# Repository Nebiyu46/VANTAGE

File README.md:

# VANTAGE

**V**ibration **AN**alysis **T**ool for **A**ppliance dia**G**nostic **E**valuation

A portable, battery-powered diagnostic instrument for predictive maintenance of domestic washing machines.

---

**Author:** Nebiyu Hailu  
**Course:** Design of Electronic Devices and Systems

## Overview

VANTAGE implements predictive maintenance by analyzing the acoustic and vibrational "fingerprint" of washing machines. Unlike reactive repair strategies, it enables proactive monitoring to detect faults before catastrophic failure occurs.

The system uses a piezoelectric contact sensor to capture mechanical vibrations, processed through a custom analog front-end with programmable gain amplification and split-path filtering. An onboard STM32 microcontroller performs real-time FFT analysis and compares signatures against learned baselines to detect incipient faults.

## Features

- **Vibration Analysis** — Real-time FFT for detecting unbalance and motor faults
- **Envelope Analysis** — High-frequency demodulation for early-stage bearing pitting detection
- **Adaptive Monitoring** — "Learn Mode" to establish statistical baselines for specific machine cycles
- **Health Metrics** — Quantitative "Health Percentage" and specific fault alerts via LCD
- **Portable Design** — Rechargeable LiPo battery with USB-C charging
- **Robust Construction** — IP54 rated enclosure for laundry room environments

## Project Structure

```
VANTAGE/
├── hardware/
│   ├── kicad/              # PCB schematic and layout (KiCad 7+)
│   │   ├── Vibration_Analyer.kicad_pro
│   │   ├── Vibration_Analyer.kicad_sch    # Main schematic
│   │   ├── Vibration_Analyer.kicad_pcb    # PCB layout
│   │   ├── mcu_sec.kicad_sch              # MCU section
│   │   └── power_section.kicad_sch        # Power supply section
│   └── enclosure/          # 3D printable enclosure (STL)
├── firmware/
│   ├── Core/               # Application source code
│   │   ├── Inc/            # Header files
│   │   └── Src/            # Source files
│   ├── Vibration_ana.ioc   # STM32CubeMX configuration
│   ├── CMakeLists.txt      # CMake build configuration
│   └── startup_stm32f401xc.s
└── docs/                   # Design documentation
    ├── Vibration Analyzer Design Report.pdf
    ├── Enclosure Drawing Part 1.pdf
    └── Enclosure Drawing Part 2.pdf
```

## Hardware Specifications

| Component | Specification |
|-----------|---------------|
| **MCU** | STM32F401RCT6 (ARM Cortex-M4 with FPU) |
| **Logic Voltage** | 3.3V |
| **ADC** | 12-bit, >2 Msps capable |
| **Display** | 128x64 Graphic LCD or 16x2 Character LCD (I2C) |
| **Battery** | Single-cell LiPo 3.7V, 1000mAh |
| **Charging** | USB-C 5V with TP4056 management |
| **Regulator** | MCP1700-3302E LDO |
| **Op-Amps** | MCP6022 (Rail-to-Rail) |
| **Sensor** | Piezoelectric contact transducer |

## Analog Front-End Architecture

```
                                            ┌──────────────┐
                                       ┌───▶│  LPF ~8kHz   │────▶ ADC (PC0)
                                       │    │ (Anti-Alias) │       Path A (FFT)
              ┌───────┐   ┌─────────┐  │    └──────────────┘
 Piezo ──▶   │ Buffer │──▶│   PGA   │──┤
              └───────┘   │ 1×-128× │  │    ┌──────────┐   ┌──────────────┐
                          └─────────┘  └───▶│ HPF >2kHz│──▶│  Envelope    │──▶ ADC (PB1)
                                            └──────────┘   │  Detector    │    Path B (Envelope)
                                                           └──────────────┘
```

- **Path A (Spectral Analysis):** 2nd-order Sallen-Key LPF (~8 kHz cutoff) for FFT
- **Path B (Feature Extraction):** HPF (~2.1 kHz) → Envelope Detector for bearing faults
- **PGA:** Digitally controlled gain (1× to 128×) via CD4051B multiplexer
- **Virtual Ground:** 1.65V reference for single-supply operation

## Fault Detection

| Fault Type | Detection Method | Frequency Range |
|------------|------------------|-----------------|
| Load Unbalance | Peak at 1× RPM | 10-20 Hz |
| Bearing Wear | Envelope analysis | >2 kHz |
| Belt Degradation | Harmonic analysis | Motor freq. |
| Electrical Fault | 100 Hz signature | 100 Hz |
| Suspension Failure | Low-freq response | <50 Hz |

## Building the Firmware

### Prerequisites
- [STM32CubeMX](https://www.st.com/en/development-tools/stm32cubemx.html)
- [ARM GCC Toolchain](https://developer.arm.com/tools-and-software/open-source-software/developer-tools/gnu-toolchain/gnu-rm)
- CMake 3.20+

### Build Steps

1. **Generate HAL Drivers** (first time only):
   ```bash
   # Open firmware/Vibration_ana.ioc in STM32CubeMX
   # Click "Generate Code" to create Drivers/ folder
   ```

2. **Build**:
   ```bash
   cd firmware
   mkdir build && cd build
   cmake ..
   make
   ```

## Environmental Design

| Specification | Value |
|---------------|-------|
| **IP Rating** | IP54 (Dust Protected / Splash Proof) |
| **Environment** | Laundry room (humidity, vibration) |
| **Enclosure** | ABS/PETG, 3D printed |
| **PCB Protection** | Acrylic conformal coating |
| **Sealing** | Silicone gaskets |
| **Operating Temp** | Up to 60°C |

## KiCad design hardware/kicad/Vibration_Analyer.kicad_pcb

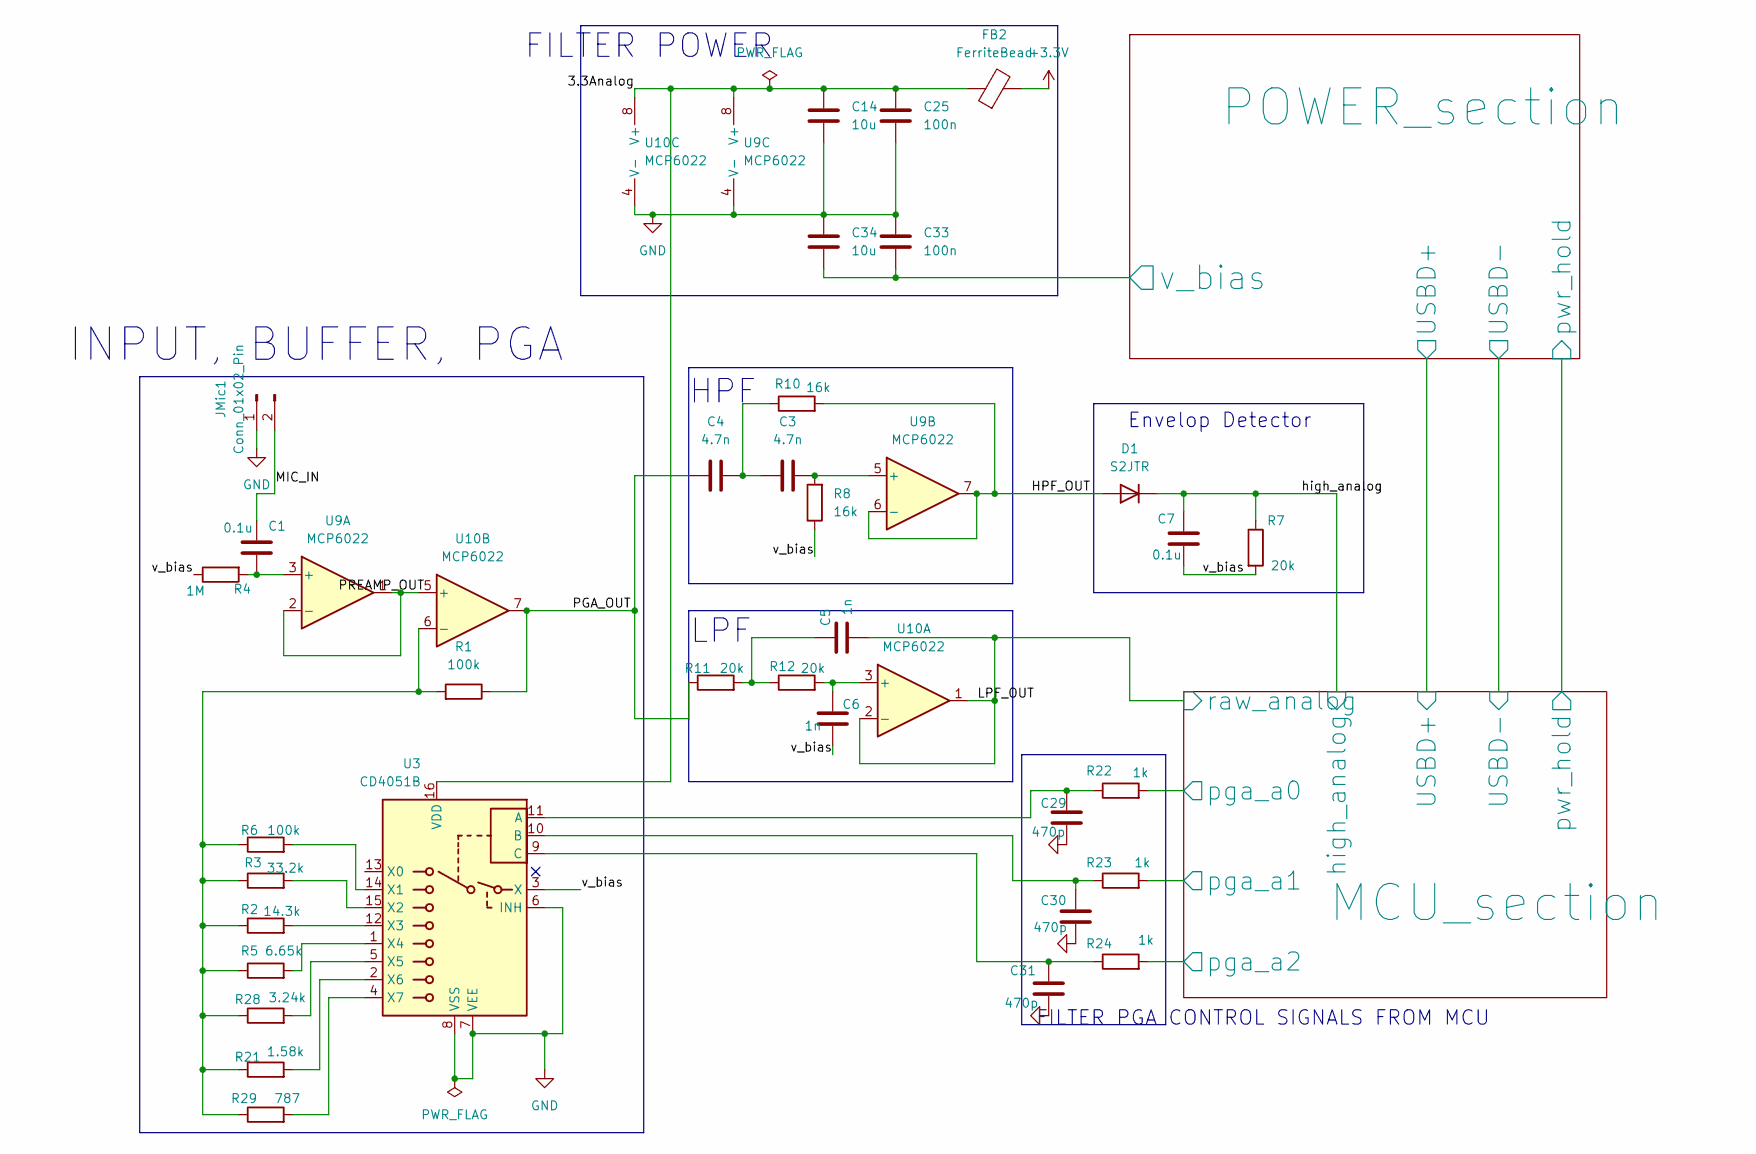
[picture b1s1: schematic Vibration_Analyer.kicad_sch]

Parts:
C1, C7: 0.1u; C_0805_2012Metric_Pad1.18x1.45mm_HandSolder
C3, C4: 4.7n; C_0805_2012Metric_Pad1.18x1.45mm_HandSolder
C5, C6: 1n; C_0805_2012Metric_Pad1.18x1.45mm_HandSolder
C14, C34: 10u; C_0805_2012Metric_Pad1.18x1.45mm_HandSolder
C25, C33: 100n; C_0805_2012Metric_Pad1.18x1.45mm_HandSolder
C29, C30, C31: 470p; C_0805_2012Metric_Pad1.18x1.45mm_HandSolder
D1: S2JTR; D_SMB
FB2: FerriteBead; L_0805_2012Metric_Pad1.05x1.20mm_HandSolder
JMic1: Conn_01x02_Pin; JST_XH_B2B-XH-A_1x02_P2.50mm_Vertical
R1, R6: 100k; R_0805_2012Metric_Pad1.20x1.40mm_HandSolder
R2: 14.3k; R_0805_2012Metric_Pad1.20x1.40mm_HandSolder
R3: 33.2k; R_0805_2012Metric_Pad1.20x1.40mm_HandSolder
R4: 1M; R_0805_2012Metric_Pad1.20x1.40mm_HandSolder
R5: 6.65k; R_0805_2012Metric_Pad1.20x1.40mm_HandSolder
R7, R11, R12: 20k; R_0805_2012Metric_Pad1.20x1.40mm_HandSolder
R8, R10: 16k; R_0805_2012Metric_Pad1.20x1.40mm_HandSolder
R21: 1.58k; R_0805_2012Metric_Pad1.20x1.40mm_HandSolder
R22, R23, R24: 1k; R_0805_2012Metric_Pad1.20x1.40mm_HandSolder
R28: 3.24k; R_0805_2012Metric_Pad1.20x1.40mm_HandSolder
R29: 787; R_0805_2012Metric_Pad1.20x1.40mm_HandSolder
U3: CD4051B; N16
U9, U10: MCP6022; DIP787W46P254L927H533Q8

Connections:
+3.3V: FB2.2; also elsewhere on the board
/HPF_OUT: D1.2 (A), R10.2, U9.6 (-), U9.7
/LPF_OUT: C5.2, U10.1, U10.2 (-); also elsewhere on the board
/MCU_section/pga_a0: R22.2; also elsewhere on the board
/MCU_section/pga_a1: R23.2; also elsewhere on the board
/MCU_section/pga_a2: R24.2; also elsewhere on the board
/MIC_IN: C1.1, JMic1.2
/PGA_OUT: C4.1, R1.1, R11.1, U10.7
/PREAMP_OUT: U9.1, U9.2 (-), U10.5 (+)
/high_analog: C7.1, D1.1 (K), R7.1; also elsewhere on the board
/v_bias: C6.2, C7.2, C33.2, C34.2, R4.1, R7.2, R8.1, U3.3 (X); also elsewhere on the board
GND: C14.2, C25.2, C29.2, C30.1, C31.2, C33.1, C34.1, JMic1.1, U3.6 (INH), U3.7 (VEE), U3.8 (VSS), U9.4 (V-), U10.4 (V-); also elsewhere on the board
unnamed: C3.2, C4.2, R10.1
unnamed: C5.1, R11.2, R12.1
unnamed: C29.1, R22.1, U3.11 (A)
unnamed: C30.2, R23.1, U3.10 (B)
unnamed: C31.1, R24.1, U3.9 (C)
unnamed: R6.2, U3.14 (X1)
unnamed: R3.2, U3.15 (X2)
unnamed: R2.2, U3.12 (X3)
unnamed: R5.2, U3.1 (X4)
unnamed: R28.2, U3.5 (X5)
unnamed: R21.2, U3.2 (X6)
unnamed: R29.2, U3.4 (X7)
unnamed: C1.2, R4.2, U9.3 (+)
unnamed: C3.1, R8.2, U9.5 (+)
unnamed: C6.1, R12.2, U10.3 (+)
unnamed: R1.2, R2.1, R3.1, R5.1, R6.1, R21.1, R28.1, R29.1, U10.6 (-)
unnamed: C14.1, C25.1, FB2.1, U3.16 (VDD), U9.8 (V+), U10.8 (V+)

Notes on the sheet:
LPF
Envelop Detector
FILTER POWER
INPUT, BUFFER, PGA
FILTER PGA CONTROL SIGNALS FROM MCU
HPF

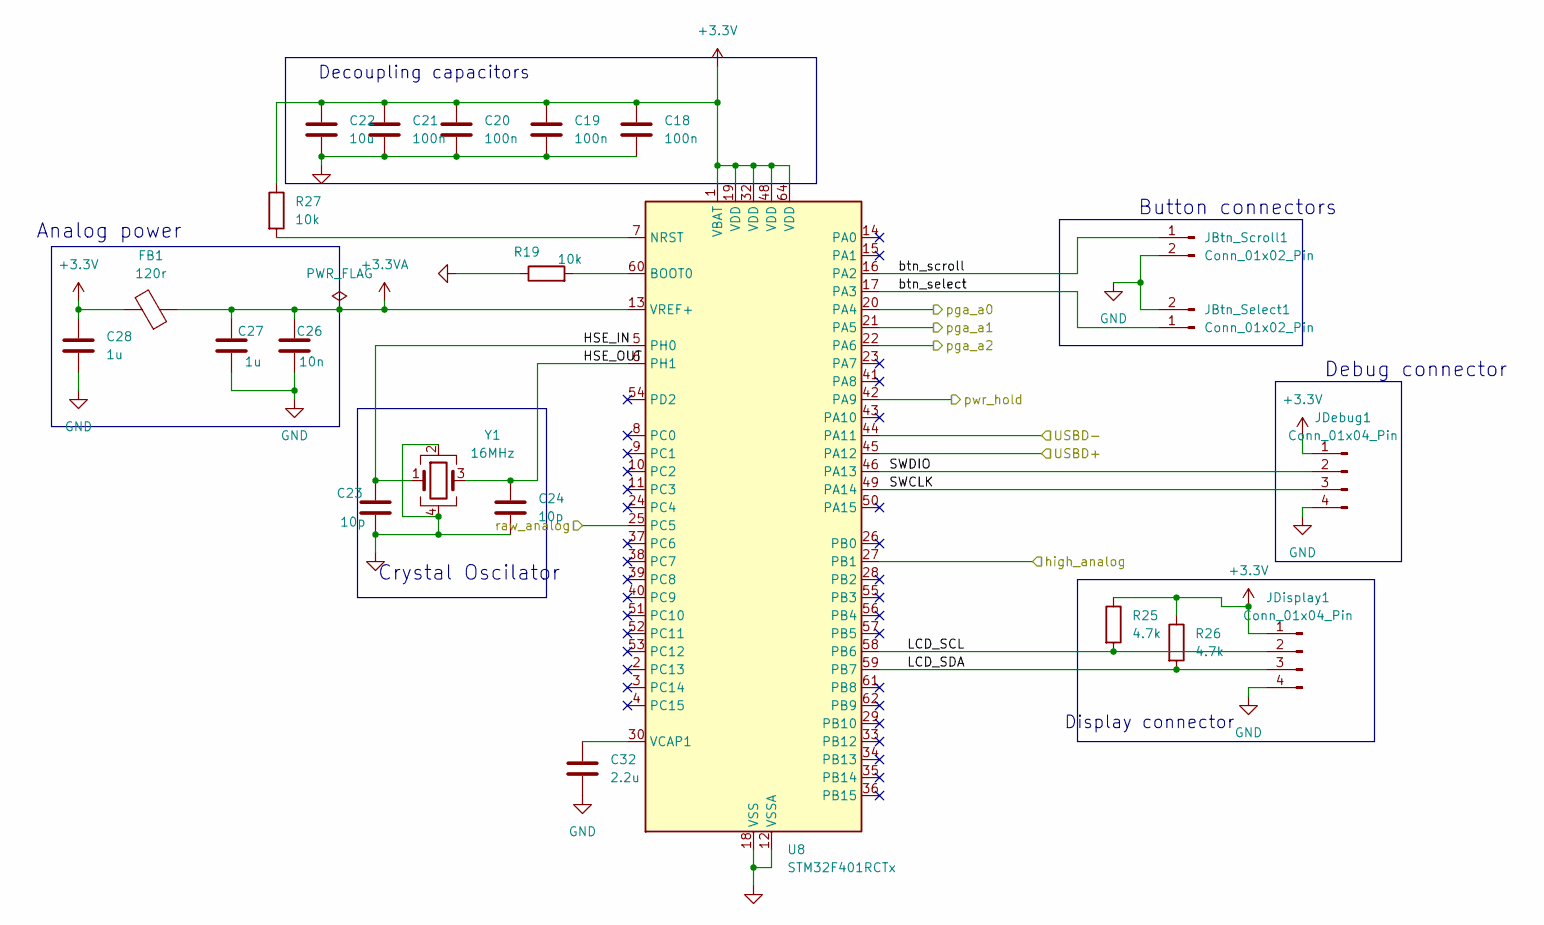
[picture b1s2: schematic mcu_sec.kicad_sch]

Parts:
C18, C19, C20, C21: 100n; C_0805_2012Metric_Pad1.18x1.45mm_HandSolder
C22: 10u; C_0805_2012Metric_Pad1.18x1.45mm_HandSolder
C23, C24: 10p; C_0805_2012Metric_Pad1.18x1.45mm_HandSolder
C26: 10n; C_0805_2012Metric_Pad1.18x1.45mm_HandSolder
C27, C28: 1u; C_0805_2012Metric_Pad1.18x1.45mm_HandSolder
C32: 2.2u; C_0805_2012Metric_Pad1.18x1.45mm_HandSolder
FB1: 120r; L_0805_2012Metric_Pad1.05x1.20mm_HandSolder
JBtn_Scroll1: Conn_01x02_Pin; JST_XH_B2B-XH-A_1x02_P2.50mm_Vertical
JBtn_Select1: Conn_01x02_Pin; JST_XH_B2B-XH-A_1x02_P2.50mm_Vertical
JDebug1: Conn_01x04_Pin; JST_XH_B4B-XH-A_1x04_P2.50mm_Vertical
JDisplay1: Conn_01x04_Pin; JST_XH_B4B-XH-A_1x04_P2.50mm_Vertical
R19, R27: 10k; R_0805_2012Metric_Pad1.20x1.40mm_HandSolder
R25, R26: 4.7k; R_0805_2012Metric_Pad1.20x1.40mm_HandSolder
U8: STM32F401RCTx; LQFP-64_10x10mm_P0.5mm
Y1: 16MHz; Crystal_SMD_3225-4Pin_3.2x2.5mm_HandSoldering

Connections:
+3.3V: C18.1, C19.1, C20.1, C21.1, C22.1, C28.1, FB1.2, JDebug1.1, JDisplay1.1, R25.1, R26.1, R27.1, U8.1 (VBAT), U8.19 (VDD), U8.32 (VDD), U8.48 (VDD), U8.64 (VDD); also elsewhere on the board
+3.3VA: C26.1, C27.1, FB1.1, U8.13 (VREF+)
/LPF_OUT: U8.25 (PC5); also elsewhere on the board
/MCU_section/HSE_IN: C23.1, U8.5 (PH0), Y1.1
/MCU_section/HSE_OUT: C24.1, U8.6 (PH1), Y1.3
/MCU_section/LCD_SCL: JDisplay1.2, R25.2, U8.58 (PB6)
/MCU_section/LCD_SDA: JDisplay1.3, R26.2, U8.59 (PB7)
/MCU_section/SWCLK: JDebug1.3, U8.49 (PA14)
/MCU_section/SWDIO: JDebug1.2, U8.46 (PA13)
/MCU_section/USBD+: U8.45 (PA12); also elsewhere on the board
/MCU_section/USBD-: U8.44 (PA11); also elsewhere on the board
/MCU_section/btn_scroll: JBtn_Scroll1.1, U8.16 (PA2)
/MCU_section/btn_select: JBtn_Select1.1, U8.17 (PA3)
/MCU_section/pga_a0: U8.20 (PA4); also elsewhere on the board
/MCU_section/pga_a1: U8.21 (PA5); also elsewhere on the board
/MCU_section/pga_a2: U8.22 (PA6); also elsewhere on the board
/MCU_section/pwr_hold: U8.42 (PA9); also elsewhere on the board
/high_analog: U8.27 (PB1); also elsewhere on the board
GND: C18.2, C19.2, C20.2, C21.2, C22.2, C23.2, C24.2, C26.2, C27.2, C28.2, C32.2, JBtn_Scroll1.2, JBtn_Select1.2, JDebug1.4, JDisplay1.4, R19.1, U8.12 (VSSA), U8.18 (VSS), U8.31 (VSS), U8.47 (VSS), U8.63 (VSS), Y1.2, Y1.4; also elsewhere on the board
unnamed: R19.2, U8.60 (BOOT0)
unnamed: R27.2, U8.7 (NRST)
unnamed: C32.1, U8.30 (VCAP1)

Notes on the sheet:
Decoupling capacitors
Analog power
Debug connector
Button connectors
Display connector
Crystal Oscilator

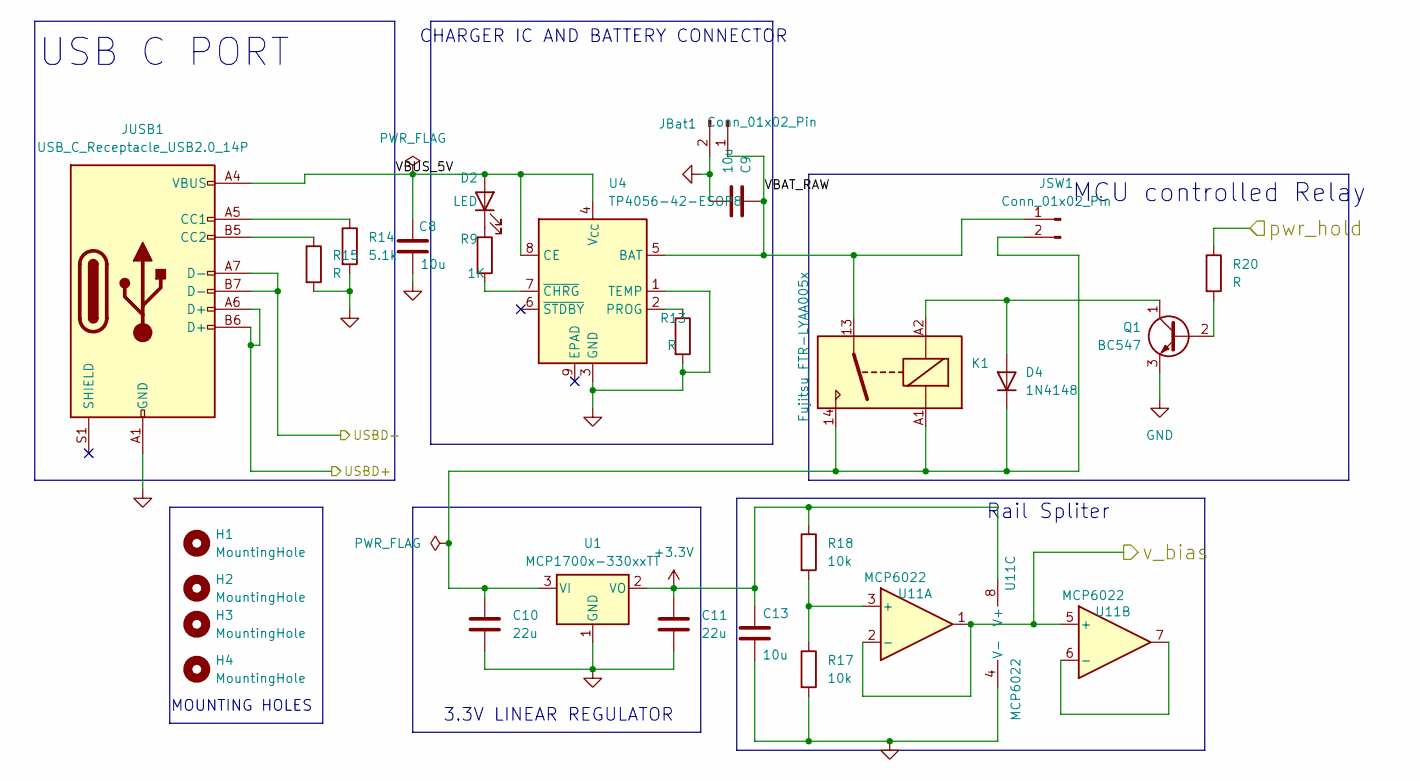
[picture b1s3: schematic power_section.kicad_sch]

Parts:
C8, C9, C13: 10u; C_0805_2012Metric_Pad1.18x1.45mm_HandSolder
C10, C11: 22u; C_0805_2012Metric_Pad1.18x1.45mm_HandSolder
D2: LED; LED_0805_2012Metric_Pad1.15x1.40mm_HandSolder
D4: 1N4148; D_DO-35_SOD27_P7.62mm_Horizontal
H1, H2, H3, H4: MountingHole; MountingHole_3.2mm_M3
JBat1: Conn_01x02_Pin; JST_XH_B2B-XH-A_1x02_P2.50mm_Vertical
JSW1: Conn_01x02_Pin; JST_EH_B2B-EH-A_1x02_P2.50mm_Vertical
JUSB1: USB_C_Receptacle_USB2.0_14P; USB_C_Receptacle_HRO_TYPE-C-31-M-12
K1: Fujitsu_FTR-LYAA005x; Relay_SPST-NO_Fujitsu_FTR-LYAA005x_FormA_Vertical
Q1: BC547; TO-92_Inline
R9: 1K; R_0805_2012Metric_Pad1.20x1.40mm_HandSolder
R13, R15, R20: R; R_0805_2012Metric_Pad1.20x1.40mm_HandSolder
R14: 5.1k; R_0805_2012Metric_Pad1.20x1.40mm_HandSolder
R17, R18: 10k; R_0805_2012Metric_Pad1.20x1.40mm_HandSolder
U1: MCP1700x-330xxTT; SOT-23
U4: TP4056-42-ESOP8; SOIC-8-1EP_3.9x4.9mm_P1.27mm_EP2.41x3.3mm_ThermalVias
U11: MCP6022; DIP787W46P254L927H533Q8

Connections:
+3.3V: C11.1, C13.1, R18.1, U1.2 (VO), U11.8 (V+); also elsewhere on the board
/MCU_section/USBD+: JUSB1.A6 (D+), JUSB1.B6 (D+); also elsewhere on the board
/MCU_section/USBD-: JUSB1.A7 (D-), JUSB1.B7 (D-); also elsewhere on the board
/MCU_section/pwr_hold: R20.1; also elsewhere on the board
/POWER_section/VBAT_RAW: C9.1, JBat1.1, JSW1.1, K1.13, U4.5 (BAT)
/POWER_section/VBUS_5V: C8.1, D2.2 (A), JUSB1.A4 (VBUS), JUSB1.A9 (VBUS), JUSB1.B4 (VBUS), JUSB1.B9 (VBUS), U4.4 (V_{CC}), U4.8 (CE)
/v_bias: U11.1, U11.2 (-), U11.5 (+); also elsewhere on the board
GND: C8.2, C9.2, C10.2, C11.2, C13.2, JBat1.2, JUSB1.A1 (GND), JUSB1.A12 (GND), JUSB1.B1 (GND), JUSB1.B12 (GND), Q1.3 (E), R13.2, R14.2, R15.2, R17.2, U1.1 (GND), U4.1 (TEMP), U4.3 (GND), U11.4 (V-); also elsewhere on the board
unnamed: D2.1 (K), R9.1
unnamed: D4.2 (A), K1.A2, Q1.1 (C)
unnamed: C10.1, D4.1 (K), JSW1.2, K1.14, K1.A1, U1.3 (VI)
unnamed: JUSB1.A5 (CC1), R14.1
unnamed: JUSB1.B5 (CC2), R15.1
unnamed: Q1.2 (B), R20.2
unnamed: R13.1, U4.2 (PROG)
unnamed: R9.2, U4.7 (~CHRG)
unnamed: R17.1, R18.2, U11.3 (+)
unnamed: U11.6 (-), U11.7

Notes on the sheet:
3.3V LINEAR REGULATOR
MOUNTING HOLES
MCU controlled Relay
Rail Spliter
CHARGER IC AND BATTERY CONNECTOR
USB C PORT

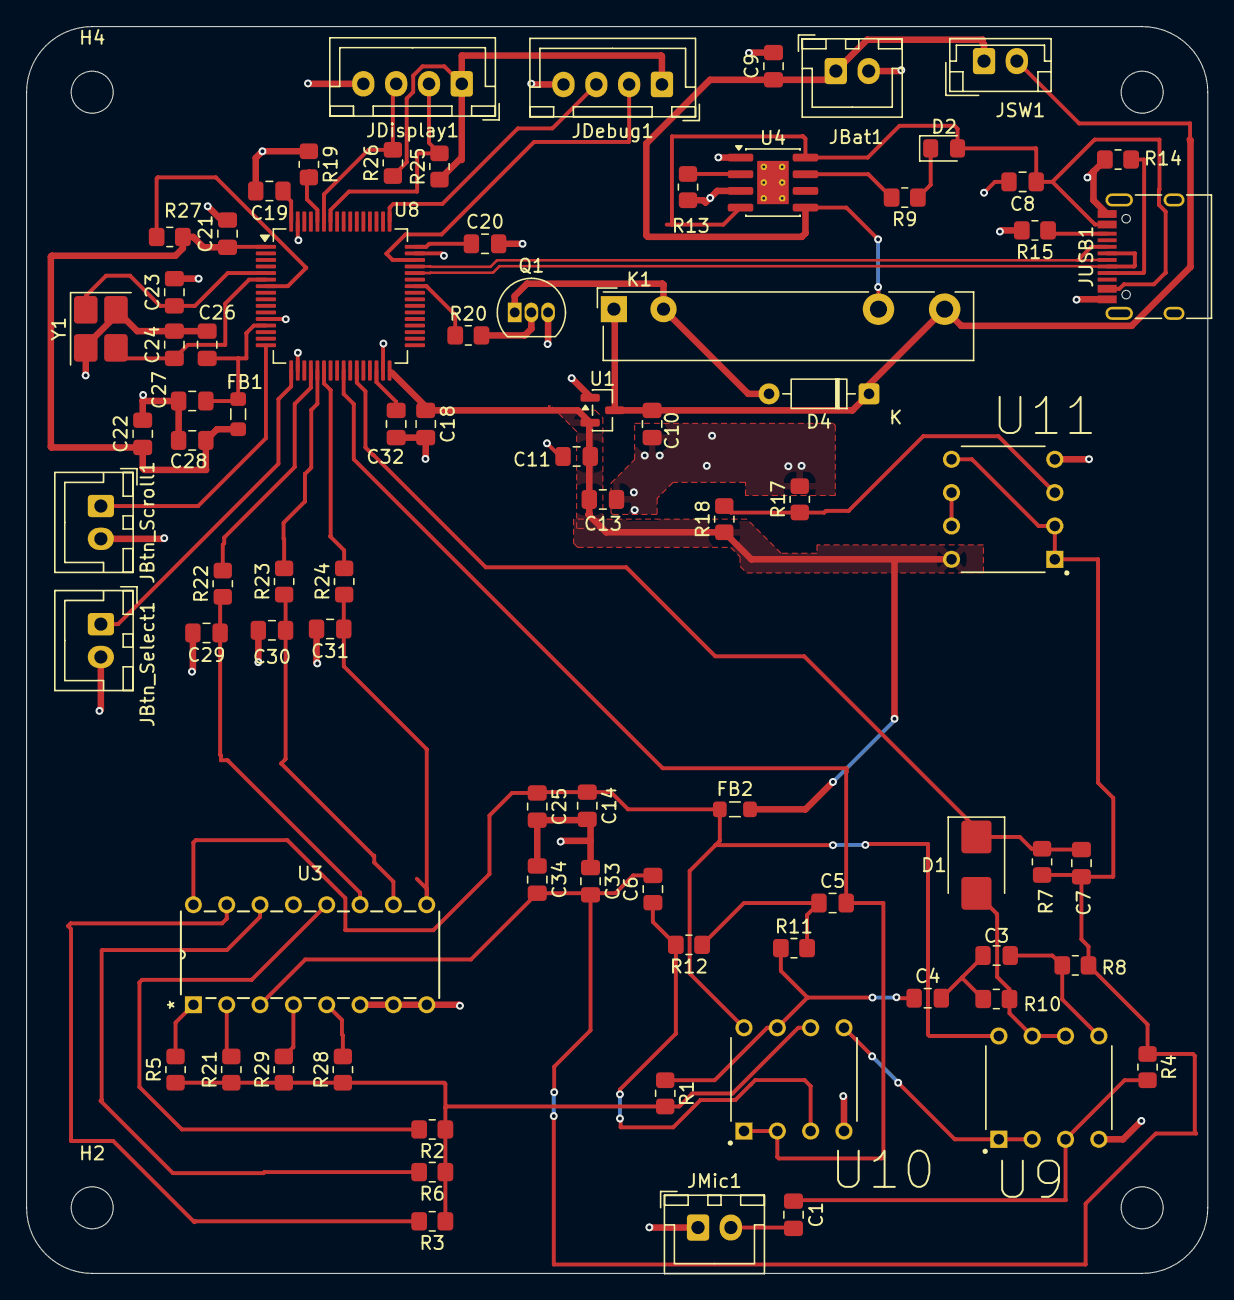
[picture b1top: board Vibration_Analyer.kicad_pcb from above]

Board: 2 copper layers, 90.0 x 95.0 mm, 84 parts (0 on the bottom side), 56 nets.

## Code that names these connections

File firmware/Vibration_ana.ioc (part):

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Mcu.Name=STM32F401R(B-C)Tx
Mcu.Package=LQFP64
Mcu.UserName=STM32F401RCTx
PA0-WKUP.GPIOParameters=GPIO_Label
PA0-WKUP.GPIO_Label=raw_In
PA0-WKUP.Signal=ADCx_IN0
PA1.GPIOParameters=GPIO_Label
PA1.GPIO_Label=high_in
PA1.Signal=ADCx_IN1
PA11.Mode=Host_Only
PA11.Signal=USB_OTG_FS_DM
PA12.Mode=Host_Only
PA12.Signal=USB_OTG_FS_DP
PA13.Mode=Serial_Wire
PA13.Signal=SYS_JTMS-SWDIO
PA14.Mode=Serial_Wire
PA14.Signal=SYS_JTCK-SWCLK
PA2.GPIOParameters=GPIO_Label
PA2.GPIO_Label=btn_scroll
PA2.Signal=GPIO_Input
PA3.GPIOParameters=GPIO_Label
PA3.GPIO_Label=btn_select
PA3.Signal=GPIO_Input
PB0.GPIOParameters=GPIO_Label
PB0.GPIO_Label=pwr_hold
PB0.Signal=GPIO_Output
PB12.GPIOParameters=GPIO_Label
PB12.GPIO_Label=pga_A0
PB12.Signal=GPIO_Output
PB13.GPIOParameters=GPIO_Label
PB13.GPIO_Label=pga_A1
PB13.Signal=GPIO_Output
PB14.GPIOParameters=GPIO_Label
PB14.GPIO_Label=pga_A2
PB14.Signal=GPIO_Output
PB6.Signal=I2C1_SCL
PB7.Signal=I2C1_SDA
PH0\ -\ OSC_IN.Mode=HSE-External-Oscillator
PH0\ -\ OSC_IN.Signal=RCC_OSC_IN
PH1\ -\ OSC_OUT.Mode=HSE-External-Oscillator
PH1\ -\ OSC_OUT.Signal=RCC_OSC_OUT
RCC.HSE_VALUE=16000000
RCC.SYSCLKFreq_VALUE=16000000
board=custom

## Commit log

2025-12-16 Initial commit: VANTAGE - Vibration Analysis Tool for Appliance Diagnostic Evaluation
2025-12-16 Fix AFE architecture diagram: HPF branches from PGA output
